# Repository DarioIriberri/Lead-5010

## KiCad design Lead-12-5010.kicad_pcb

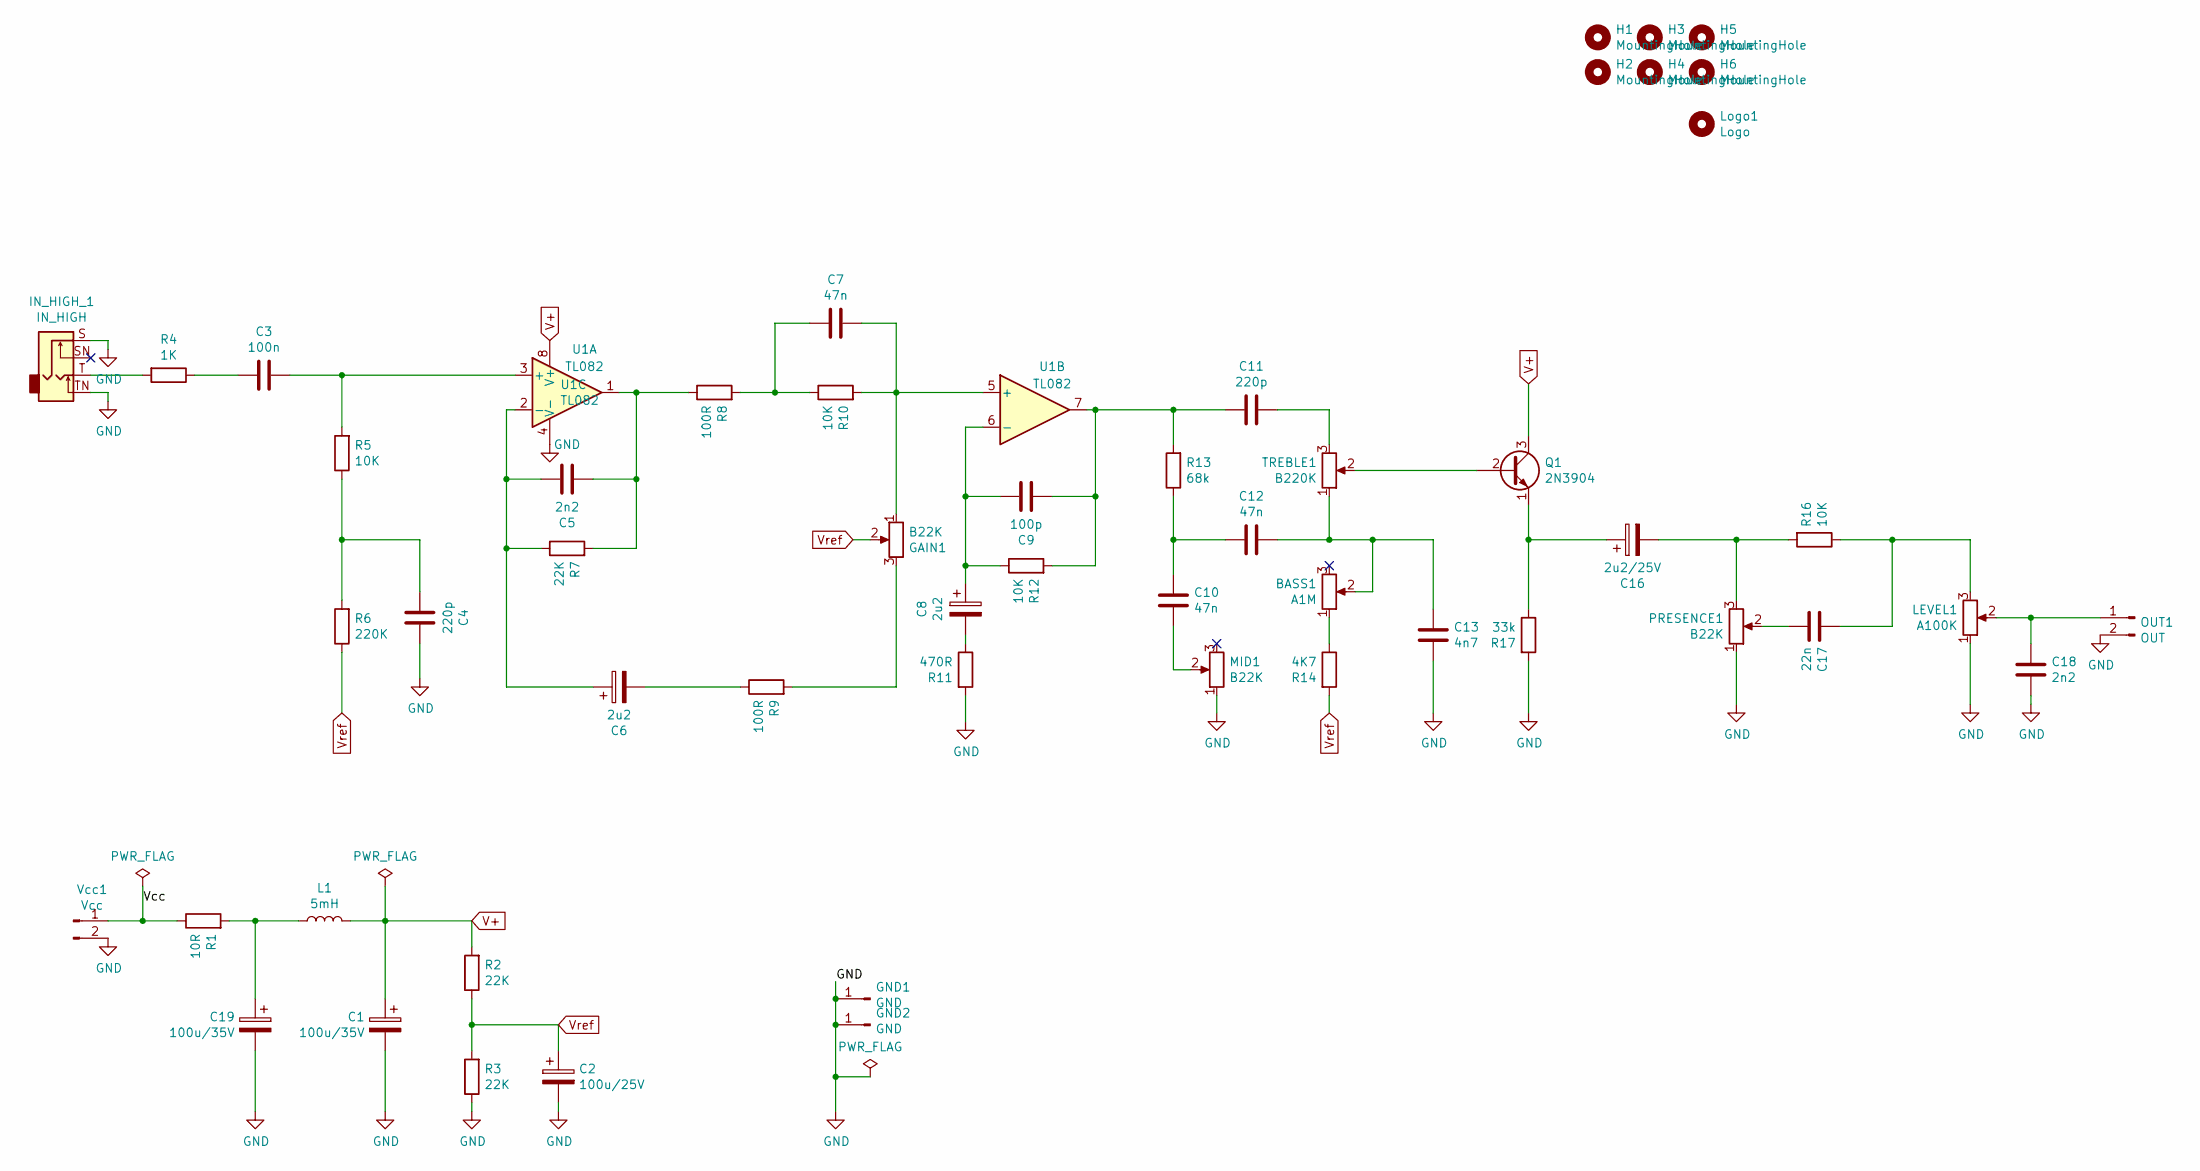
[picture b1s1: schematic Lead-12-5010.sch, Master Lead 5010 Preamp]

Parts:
BASS1: A1M; Potentiometer_Piher_T-16H_Single_Horizontal
C1, C19: 100u/35V; CP_Radial_D8.0mm_P3.50mm
C2: 100u/25V; CP_Radial_D8.0mm_P3.50mm
C3: 100n; C_Rect_L10.3mm_W5.0mm_P7.50mm_MKS4
C4, C11: 220p; C_Disc_D5.0mm_W2.5mm_P5.00mm
C5, C18: 2n2; C_Rect_L7.2mm_W3.0mm_P5.00mm_FKS2_FKP2_MKS2_MKP2
C6, C8: 2u2; CP_Radial_D8.0mm_P3.50mm
C7, C10, C12: 47n; C_Rect_L10.3mm_W5.0mm_P7.50mm_MKS4
C9: 100p; C_Disc_D5.0mm_W2.5mm_P5.00mm
C13: 4n7; C_Rect_L7.2mm_W3.0mm_P5.00mm_FKS2_FKP2_MKS2_MKP2
C16: 2u2/25V; CP_Radial_D6.3mm_P2.50mm
C17: 22n; C_Rect_L7.2mm_W3.0mm_P5.00mm_FKS2_FKP2_MKS2_MKP2
GAIN1: B22K; Potentiometer_Piher_T-16H_Single_Horizontal
GND1, GND2: GND; PinHeader_1x01_P2.54mm_Vertical
H1, H2, H3, H4, H5, H6: MountingHole; MountingHole_3.2mm_M3
IN_HIGH_1: IN_HIGH; 6.35MM_STEREO_SWITCHED_JACK
L1: 5mH; L_Radial_D6.0mm_P4.00mm
LEVEL1: A100K; Potentiometer_Piher_T-16H_Single_Horizontal
Logo1: Logo; toad
MID1: B22K; Potentiometer_Piher_T-16H_Single_Horizontal
OUT1: OUT; JST_PH_B2B-PH-K_1x02_P2.00mm_Vertical
PRESENCE1: B22K; Potentiometer_Piher_T-16H_Single_Horizontal
Q1: 2N3904; TO-92L_Inline_Wide
R1: 10R; R_Axial_DIN0207_L6.3mm_D2.5mm_P10.16mm_Horizontal
R2, R3, R7: 22K; R_Axial_DIN0207_L6.3mm_D2.5mm_P10.16mm_Horizontal
R4: 1K; R_Axial_DIN0207_L6.3mm_D2.5mm_P10.16mm_Horizontal
R5, R10, R12, R16: 10K; R_Axial_DIN0207_L6.3mm_D2.5mm_P10.16mm_Horizontal
R6: 220K; R_Axial_DIN0207_L6.3mm_D2.5mm_P10.16mm_Horizontal
R8, R9: 100R; R_Axial_DIN0207_L6.3mm_D2.5mm_P10.16mm_Horizontal
R11: 470R; R_Axial_DIN0207_L6.3mm_D2.5mm_P10.16mm_Horizontal
R13: 68k; R_Axial_DIN0207_L6.3mm_D2.5mm_P10.16mm_Horizontal
R14: 4K7; R_Axial_DIN0207_L6.3mm_D2.5mm_P10.16mm_Horizontal
R17: 33k; R_Axial_DIN0207_L6.3mm_D2.5mm_P10.16mm_Horizontal
TREBLE1: B220K; Potentiometer_Piher_T-16H_Single_Horizontal
U1: TL082; DIP-8_W7.62mm_Socket
Vcc1: Vcc; JST_PH_B2B-PH-K_1x02_P2.00mm_Vertical

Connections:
/Vcc: R1.1, Vcc1.1
GND: C1.2, C2.2, C4.1, C13.2, C18.2, C19.2, GND1.1, GND2.1, IN_HIGH_1.S, IN_HIGH_1.TN, LEVEL1.1, MID1.1, OUT1.2, PRESENCE1.1, R3.1, R11.2, R17.2, U1.4 (V-), Vcc1.2
unnamed: BASS1.1, R14.1
unnamed: BASS1.2, C12.1, C13.1, TREBLE1.1
unnamed: C3.1, R5.2, U1.3 (+)
unnamed: C3.2, R4.1
unnamed: C4.2, R5.1, R6.2
unnamed: C5.1, C6.1, R7.1, U1.2 (-)
unnamed: C5.2, R7.2, R8.1, U1.1
unnamed: C6.2, R9.1
unnamed: C7.1, GAIN1.1, R10.2, U1.5 (+)
unnamed: C7.2, R8.2, R10.1
unnamed: C8.1, C9.1, R12.1, U1.6 (-)
unnamed: C8.2, R11.1
unnamed: C10.1, C12.2, R13.1
unnamed: C10.2, MID1.2
unnamed: C11.1, TREBLE1.3
unnamed: C9.2, C11.2, R12.2, R13.2, U1.7
unnamed: C16.1, Q1.1 (E), R17.1
unnamed: C16.2, PRESENCE1.3, R16.2
unnamed: C17.1, LEVEL1.3, R16.1
unnamed: C17.2, PRESENCE1.2
unnamed: C18.1, LEVEL1.2, OUT1.1
unnamed: C19.1, L1.1, R1.2
unnamed: GAIN1.3, R9.2
unnamed: IN_HIGH_1.T, R4.2
unnamed: Q1.2 (B), TREBLE1.2
V+: C1.1, L1.2, Q1.3 (C), R2.2, U1.8 (V+)
Vref: C2.1, GAIN1.2, R2.1, R3.2, R6.1, R14.2

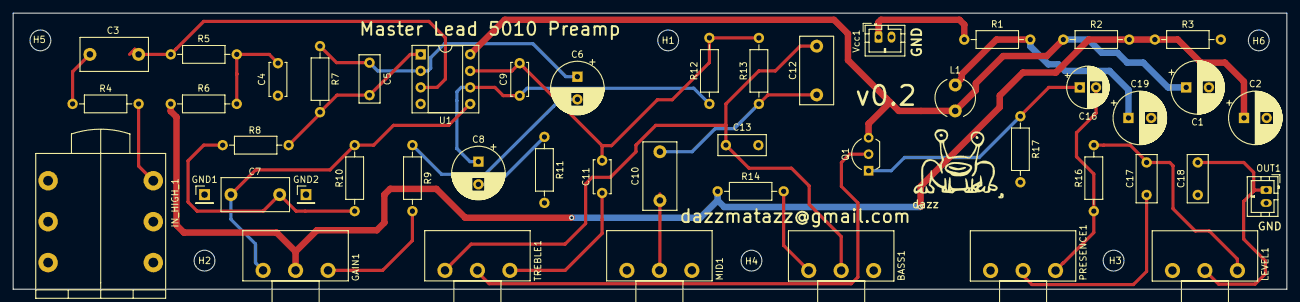
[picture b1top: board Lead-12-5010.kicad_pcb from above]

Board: 2 copper layers, 196.1 x 42.5 mm, 54 parts (0 on the bottom side), 29 nets.

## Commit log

2020-01-25 Gerbers
2020-01-25 Tweak
2020-03-07 Removed low input
2020-03-09 Added filter cap
2020-03-30 Preparing 0.2
2020-05-09 3D Path
2020-09-17 Changed output buffer to BJT, removed op amp booster
2020-09-18 New transistor footprint
2021-01-04 Removed low input. Restored output buffer. JST connectors used instead of terminal blocks.
